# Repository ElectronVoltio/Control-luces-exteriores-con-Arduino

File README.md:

# Control-luces-exteriores-con-Arduino
Programas, esquemas y PCB del circuito propuesto

Vídeo con el proyecto entero: https://youtu.be/bs5APFfVJ2o

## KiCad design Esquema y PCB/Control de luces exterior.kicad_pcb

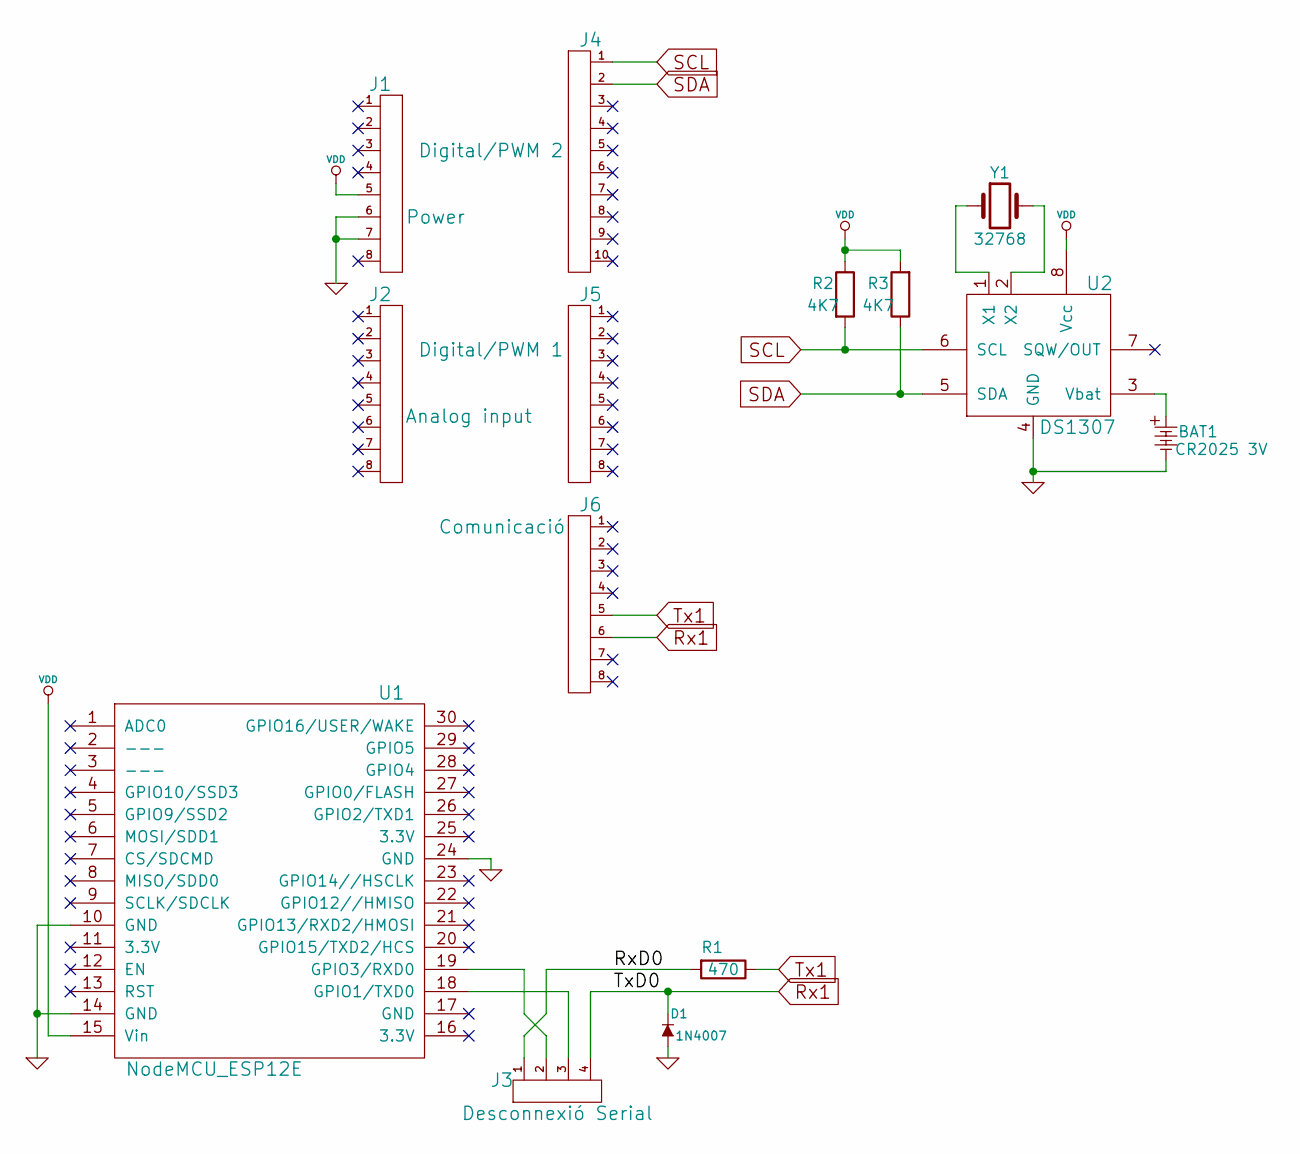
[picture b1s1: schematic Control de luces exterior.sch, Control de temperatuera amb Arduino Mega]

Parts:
BAT1: CR2025 3V; keystone_103
D1: 1N4007; diode_do35
J1: Power; pin_socket_8
J2: Analog input; pin_socket_8
J3: Desconnexió Serial; Pin_Header_Angled_1x04_Pitch2.54mm
J4: Digital/PWM 2; pin_socket_10
J5: Digital/PWM 1; pin_socket_8
J6: Comunicació; pin_socket_8
R1: 470; RC05
R2, R3: 4K7; RC05
U1: NodeMCU_ESP12E; NodeMCUESP12ELoLin
U2: DS1307; dil_8-300_socket
Y1: 32768; Crystal_AT310_d3.0mm_l10.0mm_Horizontal

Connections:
/RxD0: J3.1, R1.2
GND: BAT1.2, D1.1 (A), J1.6, J1.7, U1.10 (GND), U1.14 (GND), U1.24 (GND), U2.4 (GND)
unnamed: BAT1.1, U2.3 (Vbat)
unnamed: J3.2, U1.19 (GPIO3/RXD0)
unnamed: J3.3, U1.18 (GPIO1/TXD0)
unnamed: U2.1 (X1), Y1.1
unnamed: U2.2 (X2), Y1.2
Rx1: D1.2 (K), J3.4, J6.6
SCL: J4.1, R2.2, U2.6 (SCL)
SDA: J4.2, R3.1, U2.5 (SDA)
Tx1: J6.5, R1.1
VDD: J1.5, R2.1, R3.2, U1.15 (Vin), U2.8 (Vcc)

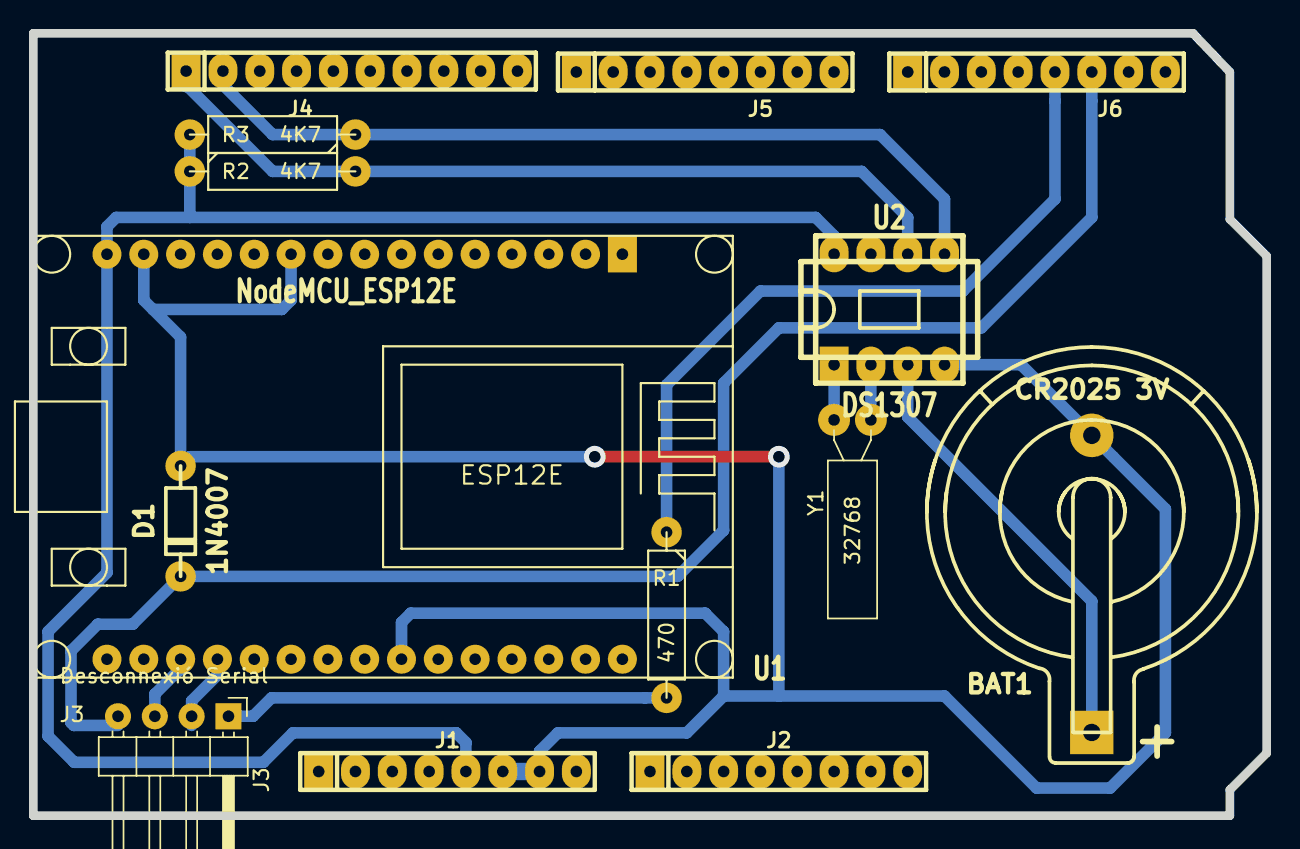
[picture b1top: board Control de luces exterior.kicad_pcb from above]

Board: 2 copper layers, 85.1 x 54.0 mm, 14 parts (0 on the bottom side), 12 nets.
